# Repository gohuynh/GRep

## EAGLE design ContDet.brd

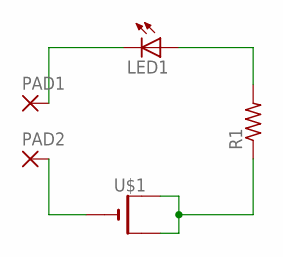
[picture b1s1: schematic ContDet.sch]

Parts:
LED1: LEDCHIPLED_0805; CHIPLED_0805
PAD1, PAD2: SMD2; SMD1,27-2,54
R1: R-US_FLIPFLOP; 0805-THM
U$1: CR1220SMT; CR1220-SMD

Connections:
unnamed: R1.1, U$1.+$1 (+), U$1.+$2 (+1)
unnamed: LED1.A, R1.2
unnamed: LED1.C, PAD1.1
unnamed: PAD2.1, U$1.-

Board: 2 copper layers, 5 parts (0 on the bottom side), 4 nets, no tracks yet.

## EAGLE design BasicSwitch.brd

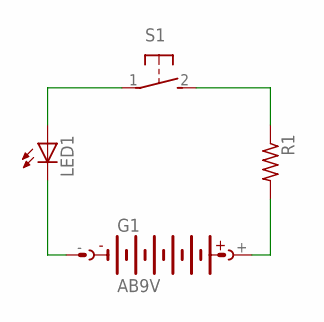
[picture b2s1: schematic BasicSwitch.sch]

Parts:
G1: AB9V
LED1: LEDCHIP-LED0805; CHIP-LED0805
R1: R-US_M0805; M0805
S1: 31-XXSKINNY; B3F-31XX-SKINNIER

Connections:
unnamed: G1.+, R1.2
unnamed: R1.1, S1.2 (S)
unnamed: LED1.A, S1.1
unnamed: G1.-, LED1.C

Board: 2 copper layers, 4 parts (0 on the bottom side), 4 nets, no tracks yet.

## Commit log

2015-09-20 Eagle Practice
    blinky schematic from tutorial 1
2015-09-20 Basic Switch schematic and board
2015-09-20 BasicSwitch and Continuity Board
2015-09-24 BME280Library
2017-04-11 Breakout Game
